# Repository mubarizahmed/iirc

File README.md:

<!-- >>>
**Project-Template**

Please use this template for your practical electronics project. (feel free to delete this section) 

You can find a quick guide in the following [cheat sheet](https://www.markdownguide.org/cheat-sheet/) or specific [gitlab style](https://docs.gitlab.com/ee/user/markdown.html) here

>>> -->

----

# Universal IR Remote Controller

by: Mubariz Ahmed and Muhammad Hadi Imtiaz

**Faculty of Technology and Bionics**

***Rhine-Waal University of Applied Sciences***

Date: XX January 2022

----

## Abstract

Short summary of the project and the work conducted

## Table of Contents

[[_TOC_]]

## 1 Introduction

### 1.1	Background
Necessary background to your work….

Chapter 1 presents….. 

Chapter 2 presents…..

## 2	Literature review
If you have conducted literature review, this would be the point to present other researchers work in that field.

## 3	Theory
If necessary please present theory in this section.

This math is inline $`a^2+b^2=c^2`$.

## 4	Methodology
How was your approach to solve the given problem/task.
This will include descriptions of the HW used as well as the SW.

This is an example how to include code snippet:
```python
def function():
    #indenting works just fine in the fenced code block
    s = "Python code"
    print s
```

Example how to draw a table:

| Left Aligned | Centered | Right Aligned |
| :---         | :---:    | ---:          |
| Cell 1       | Cell 2   | Cell 3        |
| Cell 4       | Cell 5   | Cell 6        |
| OpAmp 741    | 2        | 1.00          |

## 5	Results
Here you should present your results.

This is an example how to include image:
_Logo_on_blank_PCB.jpg "Example Image")
(C) Altzone, CC BY-SA 3.0 <https://creativecommons.org/licenses/by-sa/3.0>, via Wikimedia Commons

## 6	Discussion
Here you should discuss your results

## 7	Concluding Comments
You might want to discuss possible future work here

## 8	References

* [1]
* [2] 

## 9	Appendices

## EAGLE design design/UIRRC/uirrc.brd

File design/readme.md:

<!-- This is the folder where you save your schematic and pcb design with their related files.  -->

# Design

## Working Principle

> The ESP32 will be the brains of the entire system. The system, along with the microcontroller will be powered by a battery. The choice and configuration of the battery will be done according to the total power demand of the ESP32 as well as the rest of the components. 
>
>The IR LEDs and sensor will work in tandem as the IR reciever-transmitter system, which in turn will connected to the ESP32. Users will be able to control devices via the buttons, which will also be connected to the MCU.  
>
> To program the MCU, the USB-UART convertor will recieve signals from the USB connector and turn it into serial data for the ESP32. 

A general schematic of the system is shown below:

## Key Components

### 1. MCU
#### Requirements
- WiFi connectivity
- Good documentation and support
- Cost-effective
- Low power consumption
- X GPIO pins
- Sleep mode

#### Options
| Part | Pros | Cons | Pricing | Data Sheet|
|-----|------|------|---------|-----------|
|ESP-Wroom-32E-N16[^1]|<ul><li>BT enabled<li>Larger memory capacity<li>Community support and documentation</ul>| <ul><li>Higher power consumption<li>Larger PCB footprint</ul>|[3.60€][ESP-WROOM-32E Price]|[ESP-WROOM-32E datasheet]|
|Texas Instruments CC3220SM2ARGKT|<ul><li>Low consumption <li>Smaller PCB footprint</ul>|<ul><li>No BT capability<li>Scarce documentation<li>Lower memory capacity</ul>|[9.33€][CC3220S Price]|[CC3220S datasheet]| 

#### Selection
The ESP32 was chosen as the MCU for this project. The ESP32 is a low-cost, low-power system on a chip microcontroller with integrated Wi-Fi and dual-mode Bluetooth. 

It is a powerful, generic Wi-Fi+BT+BLE MCU module that targets a wide variety of applications, ranging from low-power sensor networks to the most demanding tasks, such as voice encoding, music streaming and MP3 decoding. The ESP32 is the successor to the popular ESP8266. The ESP32 is a perfect choice for this project as it has a built-in Wi-Fi and Bluetooth connectivity, which will be used to connect to the internet and control the devices. 

The ESP32 also has a large memory capacity, which will be used to store the code and data. The ESP32 also has a low power consumption, which will be useful for the battery-powered system. The ESP32 also has a large number of GPIO pins, which will be used to connect the IR LEDs and sensor. The ESP32 also has a sleep mode, which will be used to conserve power when the system is not in use.

### 2. IR Reciever
#### Requirements
- Frequency range: 36.7kHz-38kHz [^4]
- Electrostatic shield?
- Automatic gain control (AGC) circuit -AGC2 [^AGC2]

#### Options
| Part | Pros | Cons | Pricing | Data Sheet|
|-----|------|------|---------|-----------|
|TSMP77000|<ul><li>Wide range of frequencies 20 kHz to 60 kHz<li>Dedicated carrier out signal (modulated) for code learning <li>Improved shielding <li>Good documentation </ul> | <ul><li> Additional processing required to output signal </ul>|[1.65€][TSMP77000 Price] |[TSMP77000 Datasheet]|
|TSOP38438| <ul><li>Low supply current <li> Internal filter for required frequency 38Hz <li> Good documentation and widespread usage </ul> | <ul><li> Only 38Hz and adjacent frequencies </ul> | [1.16€][TSOP38438 Price]|[TSOP38438 Datasheet] |
|VS1838B|<ul> <li>Cheap </ul> |<ul><li>Poor documentation </ul> | [0.06€][VS1838B Price] | [VS1838B Datasheet]|

#### Selection 
TSOP38438 was selected because it is a well documented and widely used IR reciever. It also has a low supply current and an internal filter for the required frequency. 

The additional frequency range of the TSMP77000 was not required as the IR remote control will be controlling consumer electronics that use the 36.7kHz - 38kHz frequency. Also, the modulated carrier out signal provided by the TSMP77000 needs additional processing to store and output the IR code.

The VS1838B was not selected as it is cheap but has poor documentation.

### 3. IR LED/Transmitter
#### Requirements
- Frequency range: 36.7kHz-38kHz [^4]
- Low power consumption

#### Options
| Part | Pros | Cons | Pricing | Data Sheet|
|-----|------|------|---------|-----------|
|LTE-4208|<ul><li>Low power consumption <li>Good documentation </ul> | <ul><li>limited range of frequencies</ul>|[0.52€][LTE-4208 Price] |[LTE-4208 Datasheet]|
|TSAL6400| <ul><li>Wide range of frequencies 20 kHz to 60 kHz <li>Good documentation </ul> | <ul><li> Higher power consumption </ul> | [0.47€][TSAL6400 Price]|[TSAL6400 Datasheet]|

#### Selection
The LTE-4208 was selected as it has a low power consumption and good documentation. The TSAL6400 has a wide range of frequencies, but the range of frequencies for provided by the LTE-4208 are sufficient for the IR Reciever. 

The TSAL6400 wasn't selected as it also has a higher power consumption. 

### 4. USB-UART Converter module
#### Requirements
- Same voltage as MCU or have both 3.3V and 5V as options
- USB 2.0/microUSB port onboard
- Complete module, will be used off PCB (not part of BOM)

#### Selection
The CP2102 module was chosen as the USB-UART converter module. This module is needed to help program the MCU. The CP2102 is a USB to UART Bridge Controller with a Virtual COM Port interface. It is a complete module, and available at the labs, which means that it will be used off the PCB and hence won't be part of the BOM. The CP2102 also has a USB 2.0/microUSB port onboard. The CP2102 was chosen as it has been often used with the ESP32. The schematic for the connection to the module is shown at: [USB-UART Circuit](schematics/usb-uart.png)

## Power Circuitry
### Battery Selection
As most of the components in the system will be powered by the battery, the battery will be the most important component in the system. The chosen battery type for this project is a typical AAA battery. Each one provides 1.5V, and there will be 3 of these employed. This gives the MCU enough operating voltage, as well as to the rest of the system. But this will be stepped down using a voltage regulator. 

### Voltage Regulator
To help step down the 4.5V from the 3x AAA batteries, the [MIC5205-3.3YM5-TR][MIC5205-3.3YM5-TR LDO Datasheet] will be used. This is a LDO voltage step-down regulator. It will step the 4.5V down to 3.3V, which is the acceptable operating voltage for the ESP32.

## Schematics

### Power Circuitry
The power circuitry features 3 1.5V AAA Batteries, in a [pcb mounted holder][2479 AAA Battery Holder Price]. A [toggle switch][AYZ0102AGRLC Switch Price] is used switch the power supply on and off. The [MIC5205-3.3YM5-TR][MIC5205-3.3YM5-TR LDO Price] LDO voltage regulator is used to step-down the voltage to 3.3V. A 1.0µF output capacitor is used as described in the typical circuit provided in the [datasheet][MIC5205-3.3YM5-TR LDO Datasheet].

### IR Receiver Circuit
The IR reciver circuit is quite simple with the TSOP38438 pins connected to the 3.3V, GND and GPIO pins of the ESP32. The circuit is shown below:

The low-pass filter circuit for the input voltage shown in the [TSOP38438 Datasheet] was not included as we do not expect significant voltage ripple and our supply voltage is greater than 2.7V.

### IR Transmitter Circuit
The [LTE-4208 IR LED][LTE-4208 Datasheet]  is used in the transmitter circuit. It has a peak emission wavelength of 940nm, which is ideal for consumer electronics[^940NM]. A viewing angle of 20° means that we need three LEDs to get a good spread. Current limiting resistors of 100ohms are used to limit the current to about 20mA which is well below the continous forward current.  

A low-side switch is used to turn on the IR LEDs. A SOT-23 package transistor is used that meets the requirement of I<sub>C</sub> > 200mA ([CMPT3904E][CMPT3904E Datasheet]).  The low-side switch is controlled by the ESP32 GPIO pin.

The circuit is shown below:

### Toggle LED, Power LED

## USB-UART Circuit
The CP2102 USB-UART module will be used to program the ESP32. The schematic for the connection to the module is shown below:

### Button Matrix
The button matrix is used to read the button presses. The button matrix is a 3x3 matrix of buttons. The circuit is shown below:

Additinally, diodes can be used to isolate single button presses from multiple button presses.
### Main Schematic

## PCB Layout
The guidelines for the PCB layout are as follows:
- The PCB should be as small as possible
- Test your schematic and board design with ERC and DRC checks in EAGLE.
- Two via sizes available: 0.6 mm (drill 0.9 mm, pad 1.5 mm) and 1.0 mm (drill 1.5 mm, pad 2.5 mm).
- Group name should be in the copper layer, for the industrially manufactured PCBs it should be in the silkscreen (e.g. layer 25).
- As start 25 thou signal tracks, 50 thou power/gnd tracks (10-15 thou between pads - keep tracks thick – reducing size called “necking”)
- Solid polygon fill preferred

- Restric layers around smd components?

The PCB layout was first created using the autorouter:

As the result was not satisfactory, the layout was manually created. Traces of 25 thou (power) and 12 thou (signal) were used with vias of 23.622 mil. The final PCB layout is shown below:

Additional refinements were made to the PCB layout based on feedback from Mr. Kremer. The following changes were made:
- Track width increased to 0.8mm
- Via drill size increased to 0.9mm
- All SMD components moved to top layer due to manufacturing constraints
-

## References
- [Low power Wifi MCU](https://hackaday.com/2018/12/17/a-deep-dive-into-low-power-wifi-microcontrollers/)

- [Running Wifi Microcontrollers on Battery](https://blog.voneicken.com/projects/low-power-wifi-intro/)

- [Choosing an Infrared Receiver Based on AGC Type](https://www.vishay.com/docs/49860/0811wd_d.pdf)

- [Infrared Receiver ICs ATA2525/ATA2526 for Use in IR Receiver Module Applications](http://ww1.microchip.com/downloads/en/DeviceDoc/Atmel-4895-Selection-Guide-ATA2525-ATA2526_Application-Note.pdf)

- [IR Receivers - Vishay](https://www.mouser.com/pdfdocs/_ms6938.pdf)

- [ESP32 Pinout Guide](https://randomnerdtutorials.com/esp32-pinout-reference-gpios/)

- [Data Formats for IR Remote Control](https://www.vishay.com/docs/80071/dataform.pdf)

- [LiFePO4 BQ25171-Q1: Automotive, Standalone 800-mA Linear Battery Charger](https://www.ti.com/lit/ds/symlink/bq25171-q1.pdf?HQS=dis-mous-null-mousermode-dsf-pf-null-wwe&ts=1667331358610&ref_url=https%253A%252F%252Fwww.mouser.de%252F)

- [esp32-pico-kit-v4_schematic](https://dl.espressif.com/dl/schematics/esp32-pico-kit-v4_schematic.pdf)

- [Battery Protection and Power Circuitry](https://www.electronics-lab.com/lifepo4-charger-board-based-on-cn3058e/)

- [Matrix Keypads](https://www.embeddedrelated.com/showarticle/519.php)

- [Button Pad Hookup Guide](https://learn.sparkfun.com/tutorials/button-pad-hookup-guide/all)

## Footnotes
[^1]: [ESP Comparison](https://gist.github.com/sekcompsci/2bf39e715d5fe47579fa184fa819f421)

[^4]: [IR and RF remote controls](https://os.mbed.com/users/4180_1/notebook/ir-and-rf-remote-controls/#:~:text=Typically%20for%20IR%2C%20the%20frequency,most%20cases%20it%20works%20well.)

[^AGC2]: ["AGC2™ was developed for typical remote control
coding schemes with a reliable function in noisy environments"](https://www.vishay.com/docs/49860/0811wd_d.pdf)

[^940NM]: [Infrared Waves, NASA](https://science.nasa.gov/ems/07_infraredwaves#:~:text=LEFT%3A%20A%20typical%20television%20remote,to%20that%20wavelength%20of%20radiation)

[^ESP32POWER]: [ESP32 - Power Consumption by Power Modes](https://www.espressif.com/sites/default/files/documentation/esp32_datasheet_en.pdf#page=32)

[ESP-WROOM-32E Price]: https://www.mouser.de/ProductDetail/Espressif-Systems/ESP32-WROOM-32E-N16?qs=Li%252BoUPsLEnsC4cA%252BUYB2Bw%3D%3D
[ESP-WROOM-32E Datasheet]: https://www.mouser.de/datasheet/2/891/esp32_wroom_32e_esp32_wroom_32ue_datasheet_en-1855879.pdf

[CC3220S Price]: https://www.mouser.de/ProductDetail/Texas-Instruments/CC3220SM2ARGKT?qs=Mv7BduZupUjdsZg3%2FQIrGA%3D%3D
[CC3220S Datasheet]: https://www.ti.com/lit/ds/symlink/cc3220r.pdf?HQS=dis-mous-null-mousermode-dsf-pf-null-wwe&ts=1667105625183&ref_url=https%253A%252F%252Fwww.ti.com%252Fgeneral%252Fdocs%252Fsuppproductinfo.tsp%253FdistId%253D26%2526gotoUrl%253Dhttps%253A%252F%252Fwww.ti.com%252Flit%252Fgpn%252Fcc3220r

[TSMP77000 Price]:https://eu.mouser.com/ProductDetail/Vishay-Semiconductors/TSMP77000TT?qs=N%2FGwOzoYEADvNPxjOfUvfQ%3D%3D
[TSMP77000 Datasheet]: https://eu.mouser.com/datasheet/2/427/tsmp77000-1767133.pdf

[TSOP38438 Price]: https://eu.mouser.com/ProductDetail/Vishay-Semiconductors/TSOP38438?qs=fbkhFuCHoTaKUNuf%2Fea2zA%3D%3D
[TSOP38438 Datasheet]: https://eu.mouser.com/datasheet/2/427/tsop382-1145243.pdf

[VS1838B Price]: https://de.aliexpress.com/item/1005003194864725.html?spm=a2g0o.productlist.main.31.2bf3c0286xjH8g&algo_pvid=0763317b-9a37-4d71-b7fa-94616c7dab45&algo_exp_id=0763317b-9a37-4d71-b7fa-94616c7dab45-15&pdp_ext_f=%7B%22sku_id%22%3A%2212000024604334838%22%7D&pdp_npi=2%40dis%21EUR%210.66%210.66%21%21%211.82%21%21%402100b69816671508652412760d0725%2112000024604334838%21sea&curPageLogUid=w4zis35s1smo
[VS1838B Datasheet]: https://www.elecrow.com/download/Infrared%20receiver%20vs1838b.pdf

[CP2102 Price]: https://www.mouser.de/ProductDetail/Silicon-Labs/CP2102N-A02-GQFN24?qs=u16ybLDytRYKabtL%2FE7DZA%3D%3D
[CP2102 Datasheet]: https://www.mouser.de/datasheet/2/368/cp2102n_datasheet-1634912.pdf

[FT232R Price]: https://www.mouser.de/ProductDetail/FTDI/FT232RL-REEL?qs=D1%2FPMqvA103RC6OU6bKtoA%3D%3D
[FT232R Datasheet]: https://ftdichip.com/wp-content/uploads/2020/08/DS_FT232R.pdf

[LTE-4208 Price]: https://www.mouser.de/ProductDetail/Lite-On/LTE-4208?qs=YmyZEYq5wW8LrIKlCQ2NxQ%3D%3D
[LTE-4208 Datasheet]: https://www.mouser.de/datasheet/2/239/LTE-4208-1141639.pdf

[CMPT3904E Price]: https://www.mouser.de/ProductDetail/Central-Semiconductor/CMPT3904E-TR-PBFREE?qs=u16ybLDytRZdO89O3AipsA%3D%3D
[CMPT3904E Datasheet]: https://www.mouser.de/datasheet/2/68/CSEMS03188_1-2539213.pdf 

[ARGB1313HS-TR]: https://www.mouser.de/ProductDetail/Stanley-Electric/ARGB1313HS-TR?qs=byeeYqUIh0NONXvux5PuCw%3D%3D
[ARGB1313HS-TR Datasheet]: https://www.mouser.de/datasheet/2/917/downloaddatafile-1504942.pdf

[S8050 Price]: https://www.mouser.de/ProductDetail/Micro-Commercial-Components-MCC/MMSS8050-H-TP?qs=FaVZESsvgndwiDXxXq5g0g%3D%3D
[S8050 Datasheet]: https://www.mouser.de/datasheet/2/258/MMSS8050_SOT_23_-1626440.pdf

[CLP6C Price]: (https://www.mouser.de/ProductDetail/Cree-LED/CLP6C-FKB-CM1Q1H1BB7R3R3?qs=UHyCXFkX5ExeH808uCrzYg%3D%3D)
[CLP6C Datasheet]: (https://www.mouser.de/datasheet/2/723/Cree_07282021_CLP6CFKB-2498149.pdf)

[AYZ0102AGRLC Switch Price]:(https://www.mouser.de/ProductDetail/CK/AYZ0102AGRLC?qs=dJbzCyn%252BCFYWKwcWEToS6A%3D%3D)
[AYZ0102AGRLC Switch Datasheet]:(https://www.mouser.de/datasheet/2/240/ayz-3051064.pdf)

[2479 AAA Battery Holder Price]:(https://www.mouser.de/ProductDetail/Keystone-Electronics/2479?qs=Q3RoVmURDomBPD85HfXZoA%3D%3D)
[2479 AAA Battery Holder Datasheet]:(https://www.mouser.de/datasheet/2/215/2479-741518.pdf)

[MIC5205-3.3YM5-TR LDO Price]:(https://www.mouser.de/ProductDetail/Microchip-Technology-Atmel/MIC5205-3.3YM5-TR?qs=U6T8BxXiZAUfeWKvTx3acw%3D%3D)
[MIC5205-3.3YM5-TR LDO Datasheet]:(https://www.mouser.de/datasheet/2/268/MIC5205_150mA_Low_Noise_LDO_Regulator_DS20005785C-2933204.pdf)

[TSAL6400 Price]:(https://eu.mouser.com/ProductDetail/Vishay-Semiconductors/TSAL6400?qs=oSAwVt7aKTHCOCv1ythi7g%3D%3D)
[TSAL6400 Datasheet]:(https://eu.mouser.com/datasheet/2/427/tsal6400-1766599.pdf)

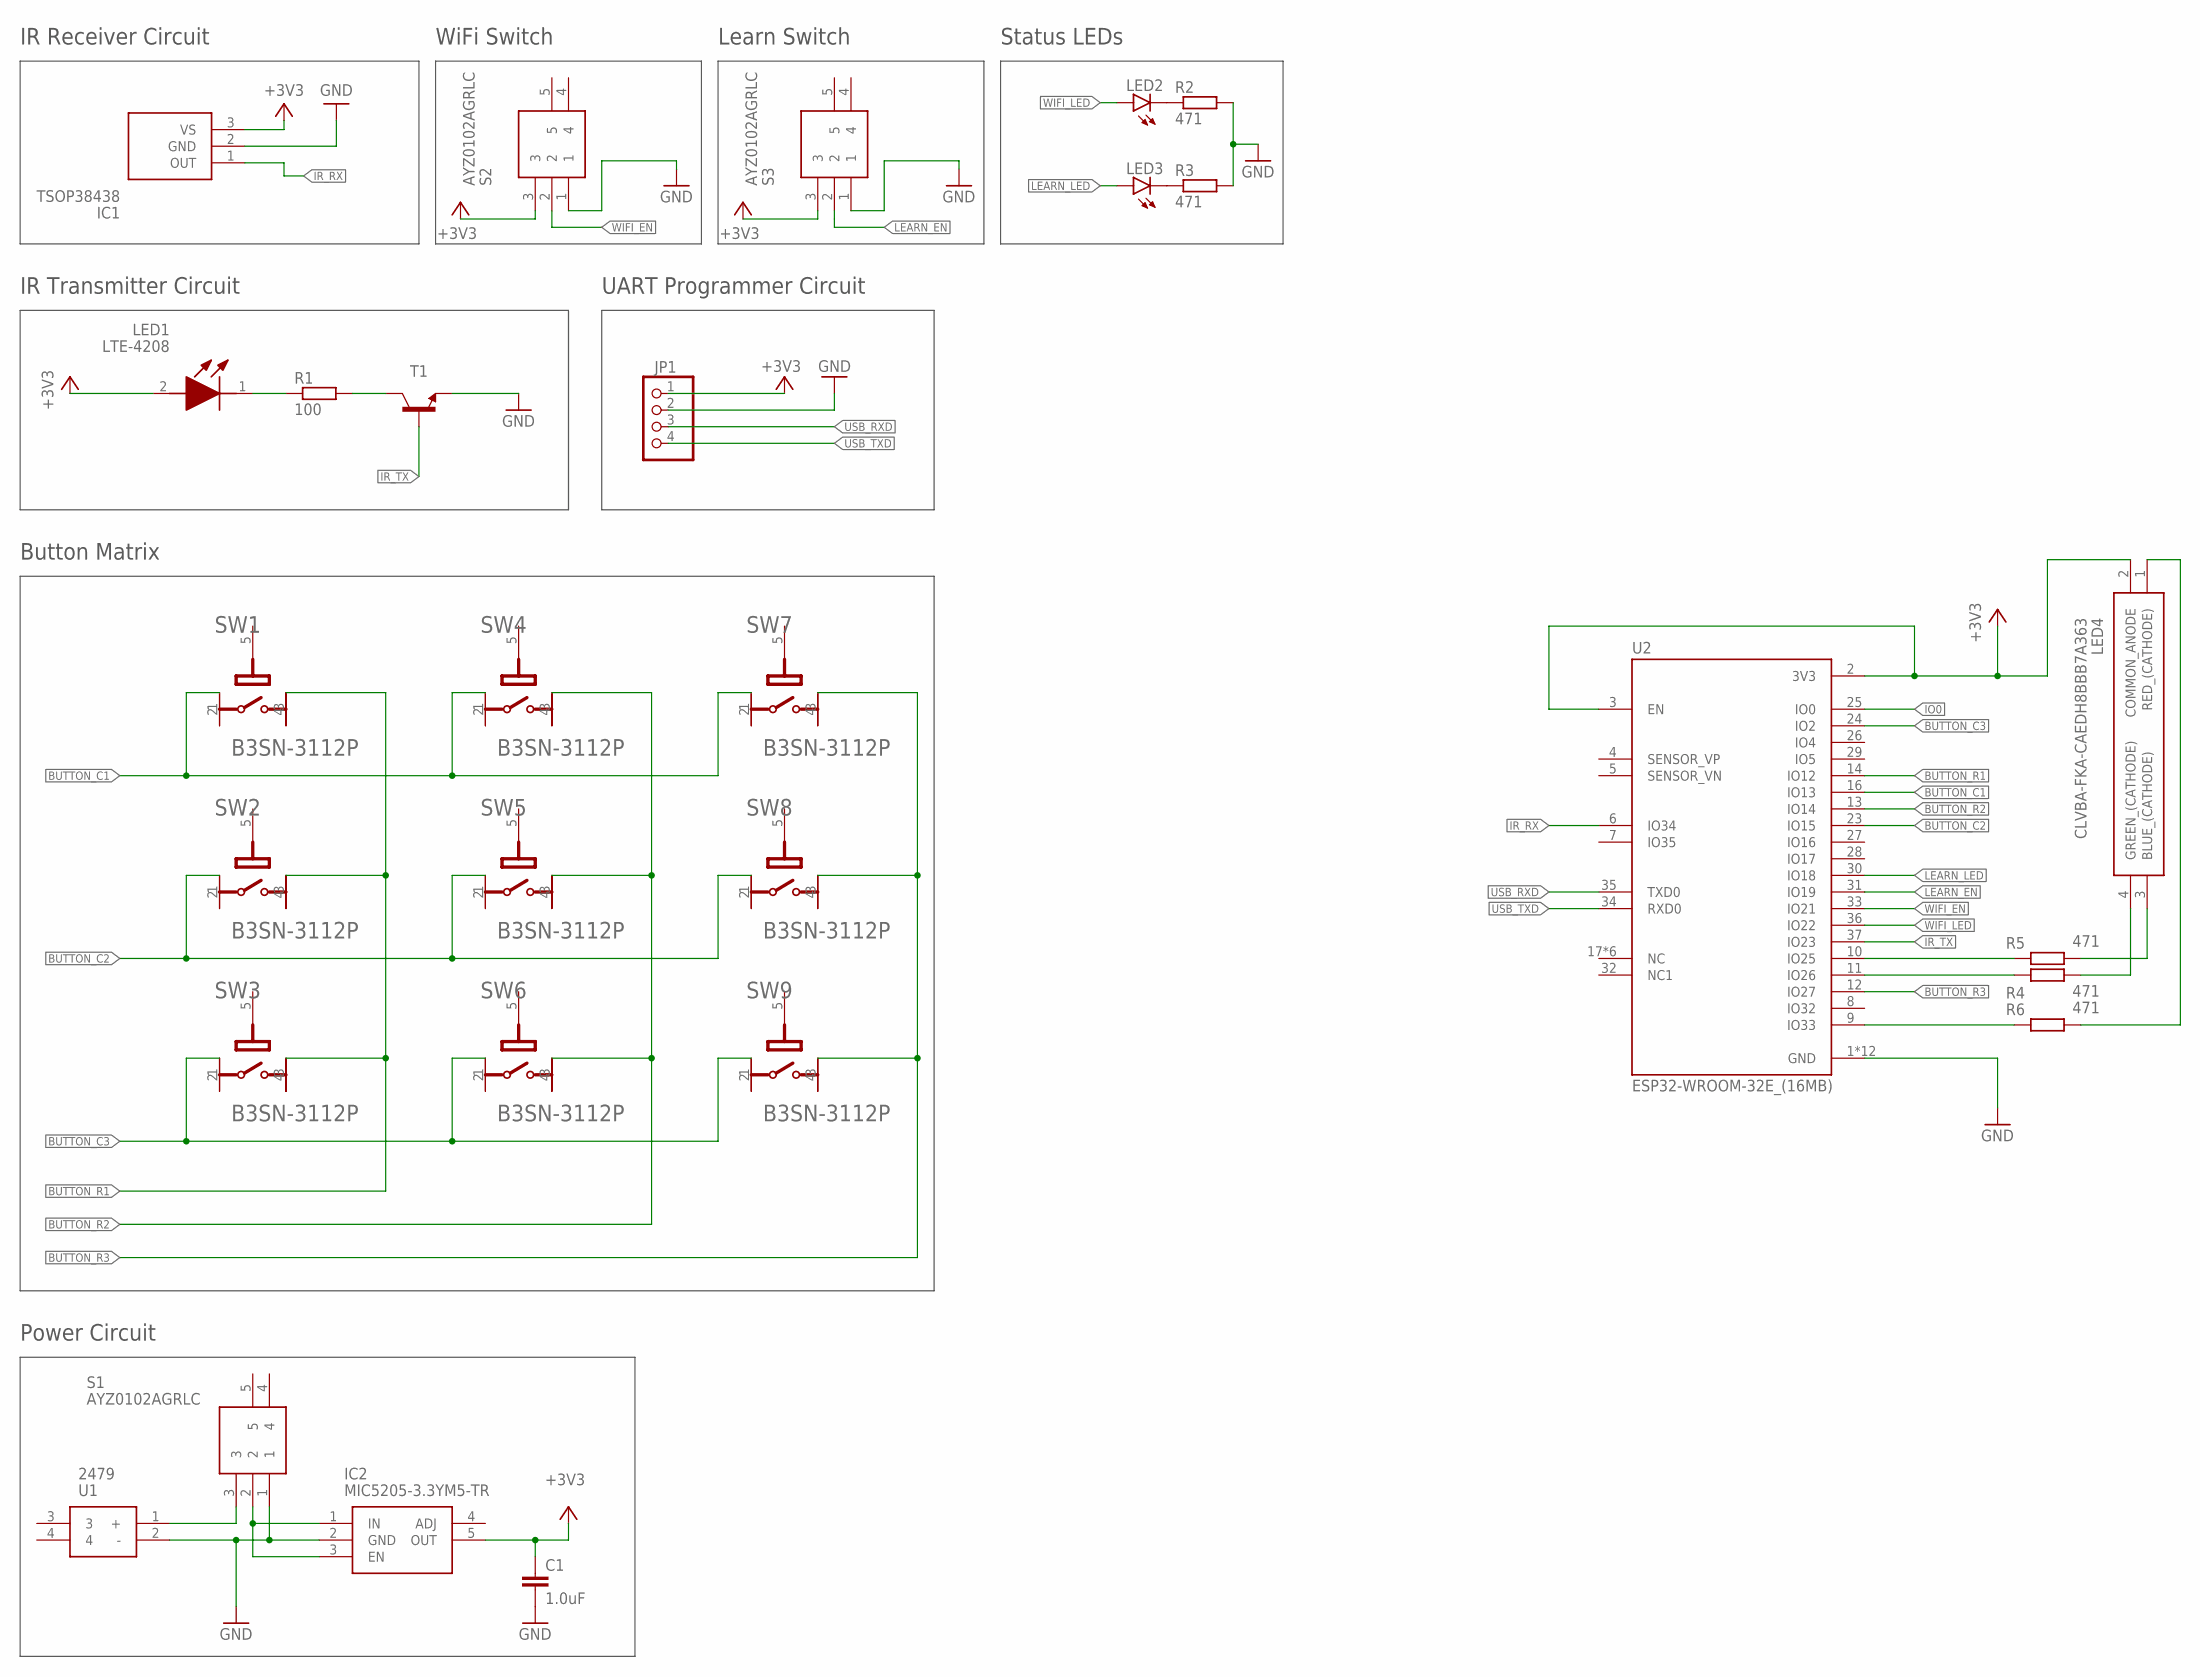
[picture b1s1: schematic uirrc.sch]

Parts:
C1: 1.0uF; C1206
IC1: TSOP38438; TSOP38238
IC2: MIC5205-3.3YM5-TR; SOT95P280X145-5N
JP1: PINHD-1X4; 1X04
LED1: LTE-4208; LTE4208
LED2, LED3: LEDCHIPLED_1206; CHIPLED_1206
LED4: CLVBA-FKA-CAEDH8BBB7A363; CLVBAFKACAEDH8BBB7A363
R1: 100; R1206
R2, R3, R4, R5, R6: 471; R1206
S1, S2, S3: AYZ0102AGRLC
SW1, SW2, SW3, SW4, SW5, SW6, SW7, SW8, SW9: OMRON_B3SN-3112POMRON_B3SN-3112P_0_0; OMRON_B3SN-3112P_0
T1: MMBT3904LT1-NPN-SOT23-BEC; SOT23-BEC
U1: 2479
U2: ESP32-WROOM-32E_(16MB); XCVR_ESP32-WROOM-32E_(16MB)

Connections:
+3V3: C1.1, IC1.3 (VS), IC2.5 (OUT), JP1.1, LED1.2 (A), LED4.2 (COMMON_ANODE), S2.3, S3.3, U2.2 (3V3), U2.3 (EN)
BUTTON_C1: SW1.1, SW4.1, SW7.1, U2.16 (IO13)
BUTTON_C2: SW2.1, SW5.1, SW8.1, U2.23 (IO15)
BUTTON_C3: SW3.1, SW6.1, SW9.1, U2.24 (IO2)
BUTTON_R1: SW1.3, SW2.3, SW3.3, U2.14 (IO12)
BUTTON_R2: SW4.3, SW5.3, SW6.3, U2.13 (IO14)
BUTTON_R3: SW7.3, SW8.3, SW9.3, U2.12 (IO27)
GND: C1.2, IC1.2 (GND), IC2.2 (GND), JP1.2, R2.2, R3.2, S1.1, S2.1, S3.1, T1.E, U1.2 (-), U2.1 (GND), U2.15 (GND), U2.38 (GND), U2.39_1 (GND), U2.39_2 (GND), U2.39_3 (GND), U2.39_4 (GND), U2.39_5 (GND), U2.39_6 (GND), U2.39_7 (GND), U2.39_8 (GND), U2.39_9 (GND)
IO0: U2.25 (IO0)
IR_RX: IC1.1 (OUT), U2.6 (IO34)
IR_TX: T1.B, U2.37 (IO23)
LEARN_EN: S3.2, U2.31 (IO19)
LEARN_LED: LED3.A, U2.30 (IO18)
unnamed: LED1.1 (K), R1.1
unnamed: R1.2, T1.C
unnamed: LED4.4 (GREEN_(CATHODE)), R4.2
unnamed: LED4.3 (BLUE_(CATHODE)), R5.2
unnamed: LED4.1 (RED_(CATHODE)), R6.2
unnamed: S1.3, U1.1 (+)
unnamed: R4.1, U2.11 (IO26)
unnamed: R5.1, U2.10 (IO25)
unnamed: R6.1, U2.9 (IO33)
unnamed: IC2.1 (IN), IC2.3 (EN), S1.2
unnamed: LED3.C, R3.1
unnamed: LED2.C, R2.1
USB_RXD: JP1.3, U2.35 (TXD0)
USB_TXD: JP1.4, U2.34 (RXD0)
WIFI_EN: S2.2, U2.33 (IO21)
WIFI_LED: LED2.A, U2.36 (IO22)

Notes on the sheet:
IR Transmitter Circuit
IR Receiver Circuit
UART Programmer Circuit
WiFi Switch
Learn Switch
Status LEDs
Power Circuit
Button Matrix

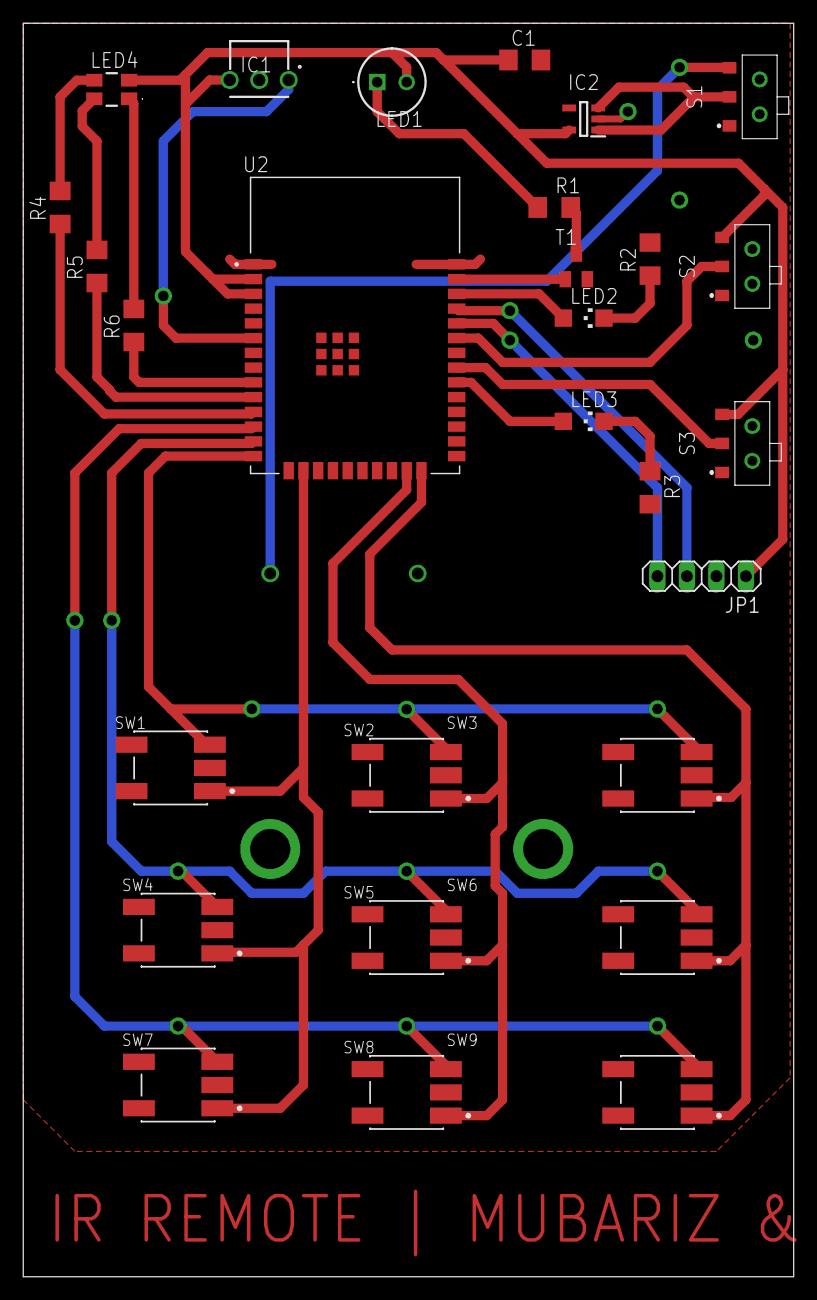
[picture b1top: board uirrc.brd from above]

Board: 2 copper layers, 66.3 x 107.9 mm, 29 parts (1 on the bottom side), 28 nets.

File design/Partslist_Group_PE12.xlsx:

Group no. |  | 12 |  |  |  | Project | Universal IR Remote
Date |  | 17/11/2022 |  |  |  | Team members | Mubariz Ahmed, Muhammad Hadi Imtiaz
No. | Qty. | manufacturer | component | ordering code (manufacturer) | vendor | ordering code (vendor) | Price per unit €* | Price €* | Link
1 | 1 | Espressif | ESP32 Compute Chip | ESP32-WROOM-32E-N16 | Mouser | 356-ESP32WRM32E128PH | 3.6 |  | https://eu.mouser.com/ProductDetail/Espressif-Systems/ESP32-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
2 | 1 | Vishay Semiconductors | IR Reciever | TSOP38438 | Mouser | 78-TSOP38438 | 1.16 |  | https://eu.mouser.com/ProductDetail/Vishay-Semiconductors/TS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
3 | 1 | Keystone Electronics | AAA battery holder | 2479 | Mouser | 534-2479 | 1.54 |  | https://eu.mouser.com/ProductDetail/Keystone-Electronics/247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
4 | 1 | Logilink | 8 x AAA battery | LR03F8 | Reichelt | LOGILINK LR03F8 | 1.85 |  | https://www.reichelt.de/de/en/alkaline-battery-aaa-pack-of-8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
5 | 1 | Microchip Technology / Atmel | LDO Voltage Regulator | MIC5205-3.3YM5-TR | HSRW | 845 | 0.36 |  | https://ee.hsrw.org/
6 | 1 | Lite-On | IR LED | LTE-4208 | Mouser | 859-LTE4208 | 0.52 |  | https://eu.mouser.com/ProductDetail/Lite-On/LTE-4208?qs=YmyZ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
7 | 1 | Central Semiconductor | NPN BJT | CMPT3904E TR PBFREE | Mouser | 610-CMPT3904E | 0.44 |  | https://eu.mouser.com/ProductDetail/Central-Semiconductor/CM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
8 | 3 | C&K | Slide switch | AYZ0102AGRLC | HSRW | 875 | 1.02 |  | https://ee.hsrw.org/
9 | 9 | Omron | SWITCH TACTILE SPST-NO 0.05A 24V | B3SN-3112P | HSRW | 876 | 0.95 |  | https://ee.hsrw.org/
10 | 2 | Lite-On | LED GREEN CLEAR 1206 SMD | LTST-C150GKT | HSRW | 848 | 0.28 |  | https://ee.hsrw.org/
11 | 1 | Cree | RGB LED | CLV1A-FKB-CK1VW1DE1BB7C3C3 | HSRW | 846 | 0.3 |  | https://ee.hsrw.org/
12 | 1 | Connectors | Single Print Connector Straight 4-Pin Pitch 2,54 mm | PSS 254/4G | HSRW | 174 | 0.06 |  | https://ee.hsrw.org/
13
14
15
 |  |  |  |  |  | total price*
List of suitable vendors: |  |  |  |  |  | value added tax (VAT)
shop |  | language | homepage |  |  | total price inclusive VAT:
HSRW |  | en | https://ee.hsrw.org/
Mouser |  | en/de | https://www.mouser.de/
Reichelt |  | en/de | https://www.reichelt.de/ |  |  |  | *without value added tax (VAT)
Conrad |  | en/de | https://www.conrad.biz/
Other |  |  | only when absolutely necessary

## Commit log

2022-10-04 Added Author
2022-10-04 Added author name
2022-10-04 Added project ideas
2022-10-04 minor change to ideas
2022-10-04 Added further ideas
2022-10-10 Added Project Decription
2022-10-13 Added Key Tasks
2022-10-30 Initialized eagel project, design documentation
2022-10-30 Added requirements, selection criteria for parts.
2022-10-30 Fixes #1
2022-10-31 Fixes #3
2022-11-01 Fixes #4
2022-11-02 Added USB-UART schematic
2022-11-02 Added schematic as design block and image
2022-11-02 Updated power circuitry
2022-11-02 Added main schematic without power circuit
2022-11-16 Fixes #9
2022-11-16 Fixes #5
2022-11-16 UART Programmer offboarded
2022-11-16 Fixes #8
2022-11-16 Fixes #10
2022-11-16 Added PCB guidelines
2022-11-17 Changes made to readme and parts list added
2022-11-17 Updated parts list
2022-11-17 Fixes #12
2022-12-08 Updated board design
2022-12-08 Updated design description
2023-12-10 add uml
2023-12-30 add: init platform.io project, test ir tx and rx
